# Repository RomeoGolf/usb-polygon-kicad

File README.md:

# USB-polygon (KiCAD)

Схема электрическая принципиальная и печатная плата отладочного устройства на базе микроконтроллера AT90USB162

## Краткое описание

Часть радиолюбительского проекта с целью создания простого устройства на микроконтроллере, имеющего возможность подключения к компьютеру по USB. Проект описан в цикле статей по адресу <http://romeogolf.github.io/tag/usb-polygon.html>.

Подробности использования платы в рамках проекта описаны в статьях цикла. Репозиторий содержит два коммита. Первый относится к статье [USB-polygon-2: Схема и плата](http://romeogolf.github.io/usb-polygon-2.html), второй --- к статье [USB-polygon-20: Мышиный энкодер](http://romeogolf.github.io/usb-polygon-20.html). Во втором коммите добавлены элементы в схему электрическую принципиальную без внесения их в печать, так как доработка выполнялась навесным монтажом, перемычками.

![Плата в KiCAD][pre_pcb]
![Вид со стороны контроллера][pre_cpu]
![Вид со стороны навесных элементов][pre_led]

[pre_pcb]: http://romeogolf.github.io/images/usb-polygon/02/preview/face-cad-small.png "Плата"
[pre_cpu]: http://romeogolf.github.io/images/usb-polygon/02/preview/cpu-small.jpg "Вид со стороны контроллера"
[pre_led]: http://romeogolf.github.io/images/usb-polygon/02/preview/led-small.jpg "Вид со стороны навесных элементов"

### Остальные части проекта:

* программа на C для микроконтроллера устройства [(ссылка)](https://github.com/RomeoGolf/usb-polygon-embedded)
* программа на C++ для взаимодействия с устройством со стороны ПК [(ссылка)](https://github.com/RomeoGolf/usb-polygon-cpp)
* программа на С++ для опроса одного из "файлов" на устройстве в непрерывном режиме (с отключением буферизации данных на ПК) [(ссылка)](https://github.com/RomeoGolf/usb-polygon-read-loop)
* программа на С++ для подготовки кадров "циферблата", отображаемого на ЖК-экране [(ссылка)](https://github.com/RomeoGolf/usb-polygon-makedial)

## Начало работы

### Зависимости

Для просмотра и внесения изменений необходим [KiCAD](http://kicad-pcb.org/).

### Получение

Для получения копии репозитория следует воспользоваться кнопкой "Clone or download" на [странице репозитория](https://github.com/RomeoGolf/usb-polygon-kicad).

При отсутствии git можно нажать кнопку "Download ZIP" и получить последнюю версию без истории коммитов.

При наличии git можно скопировать URL https://github.com/RomeoGolf/usb-polygon-kicad.git и использовать его в команде

~~~~
git clone https://github.com/RomeoGolf/usb-polygon-kicad.git
~~~~

в командной строке (git bash, например, в зависимости от ОС и настроек).

Далее можно открыть в KiCad файл "polygon.pro" и работать с проектом.

## Развитие проекта

Дальнейшее развитие проекта не предполагается, так как цель достигнута.

## Лицензия

This project is licensed under the MIT License - see the [License.txt](License.txt) file for details

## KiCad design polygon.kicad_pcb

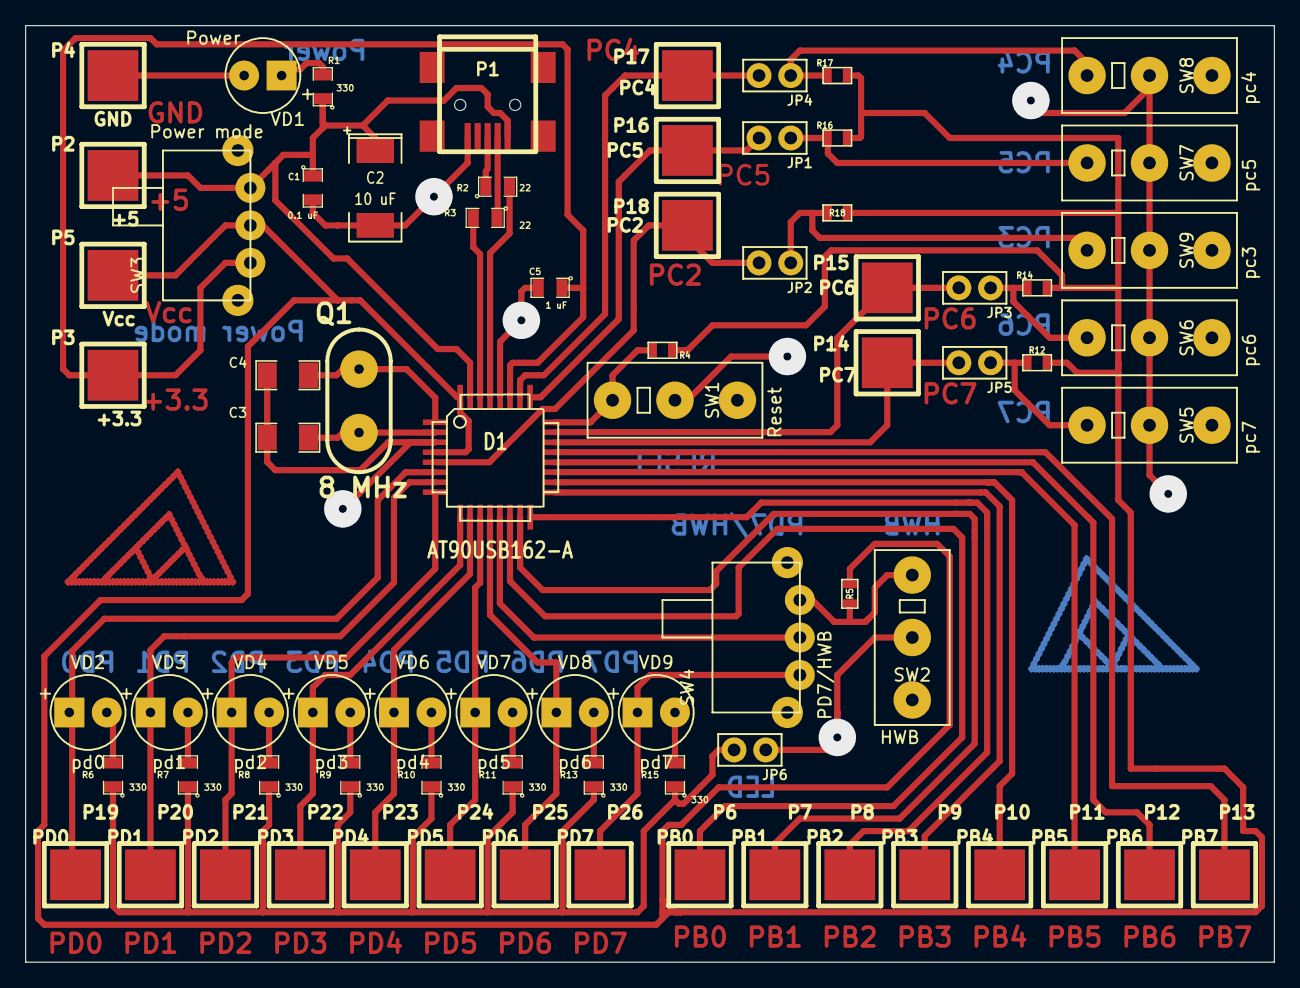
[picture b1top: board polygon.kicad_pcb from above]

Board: 2 copper layers, 100.0 x 75.0 mm, 75 parts (0 on the bottom side), 49 nets.

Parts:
C1: 0.1 uF; SM0805
C2: 10 uF; SM2512
C3, C4: 22 pF; SM1206
C5: 1 uF; SM0805
D1: AT90USB162-A; TQFP32
JP1: pc5; JUMPER
JP2: pc3; JUMPER
JP3: pc6; JUMPER
JP4: pc4; JUMPER
JP5: pc7; JUMPER
JP6: LED; JUMPER
P1: USB-MINI-B; USB__MINI_B
P2: +5; 1PIN_SMD
P3: +3.3; 1PIN_SMD
P4: GND; 1PIN_SMD
P5: Vcc; 1PIN_SMD
P6: PB0; 1PIN_SMD
P7: PB1; 1PIN_SMD
P8: PB2; 1PIN_SMD
P9: PB3; 1PIN_SMD
P10: PB4; 1PIN_SMD
P11: PB5; 1PIN_SMD
P12: PB6; 1PIN_SMD
P13: PB7; 1PIN_SMD
P14: PC7; 1PIN_SMD
P15: PC6; 1PIN_SMD
P16: PC5; 1PIN_SMD
P17: PC4; 1PIN_SMD
P18: PC2; 1PIN_SMD
P19: PD0; 1PIN_SMD
P20: PD1; 1PIN_SMD
P21: PD2; 1PIN_SMD
P22: PD3; 1PIN_SMD
P23: PD4; 1PIN_SMD
P24: PD5; 1PIN_SMD
P25: PD6; 1PIN_SMD
P26: PD7; 1PIN_SMD
Q1: 8 MHz; QUARTZ_5mm
R1, R6, R7, R8, R9, R10, R11, R13, R15: 330; SM0805
R2, R3: 22; SM0805
R4, R5, R12, R14, R16, R17, R18: 10 k; SM0603
SW1: Reset; SW_MOUSE
SW2: HWB; SW_MOUSE
SW3: Power mode; switch3
SW4: PD7/HWB; switch3
SW5: pc7; SW_MOUSE
SW6: pc6; SW_MOUSE
SW7: pc5; SW_MOUSE
SW8: pc4; SW_MOUSE
SW9: pc3; SW_MOUSE
VD1: Power; LED_3MM
VD2: pd0; LED_3MM
VD3: pd1; LED_3MM
VD4: pd2; LED_3MM
VD5: pd3; LED_3MM
VD6: pd4; LED_3MM
VD7: pd5; LED_3MM
VD8: pd6; LED_3MM
VD9: pd7; LED_3MM

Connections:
+3.3V: C5.1, D1.27, P3.1, SW3.3
+5V: C1.1, C2.1, D1.31, P1.1, P2.1, R1.1, SW3.1
GND: C1.2, C2.2, C3.1, C4.1, C5.2, D1.3, D1.28, JP6.2, P1.5, P4.1, SW1.3, SW2.3, SW5.3, SW6.3, SW7.3, SW8.3, SW9.3, VD1.2
unnamed: JP3.2, R14.2, SW6.2
unnamed: D1.15, P7.1
unnamed: D1.14, P6.1
unnamed: D1.20, P12.1
unnamed: D1.17, P9.1
unnamed: D1.18, P10.1
unnamed: D1.19, P11.1
unnamed: JP2.2, R18.2, SW9.2
unnamed: JP4.2, R17.2, SW8.2
unnamed: JP1.2, R16.2, SW7.2
unnamed: JP5.2, R12.2, SW5.2
unnamed: D1.22, JP5.1, P14.1
unnamed: D1.26, JP4.1, P17.1
unnamed: D1.25, JP1.1, P16.1
unnamed: D1.23, JP3.1, P15.1
unnamed: D1.21, P13.1
unnamed: D1.16, P8.1
unnamed: D1.8, P21.1, VD4.1
unnamed: D1.6, P19.1, VD2.1
unnamed: D1.7, P20.1, VD3.1
unnamed: D1.9, P22.1, VD5.1
unnamed: D1.13, SW4.2
unnamed: R5.1, SW2.2, SW4.1
unnamed: D1.5, JP2.1, P18.1
unnamed: P1.3, R2.1
unnamed: P1.2, R3.1
unnamed: R1.2, VD1.1
unnamed: D1.24, R4.1, SW1.2
unnamed: R15.2, VD9.2
unnamed: P26.1, SW4.3, VD9.1
unnamed: R13.2, VD8.2
unnamed: D1.12, P25.1, VD8.1
unnamed: R11.2, VD7.2
unnamed: D1.11, P24.1, VD7.1
unnamed: R10.2, VD6.2
unnamed: D1.10, P23.1, VD6.1
unnamed: R9.2, VD5.2
unnamed: R8.2, VD4.2
unnamed: R7.2, VD3.2
unnamed: R6.2, VD2.2
unnamed: D1.30, R3.2
unnamed: C3.2, D1.2, Q1.1
unnamed: D1.29, R2.2
unnamed: JP6.1, R6.1, R7.1, R8.1, R9.1, R10.1, R11.1, R13.1, R15.1
unnamed: C4.2, D1.1, Q1.2
VCC: D1.4, D1.32, P5.1, R4.2, R5.2, R12.1, R14.1, R16.1, R17.1, R18.1, SW3.2

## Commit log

2018-04-03 Initial commit
    На самом деле, завершенная схема и плата.
2018-04-03 Добавление энкодера в сему электрическую принципиальную
    без правки разводки платы, новые элементы только на схеме
2018-04-07 Добавил файл лицензии MIT
2018-04-12 License file was formatted, readme file was added
